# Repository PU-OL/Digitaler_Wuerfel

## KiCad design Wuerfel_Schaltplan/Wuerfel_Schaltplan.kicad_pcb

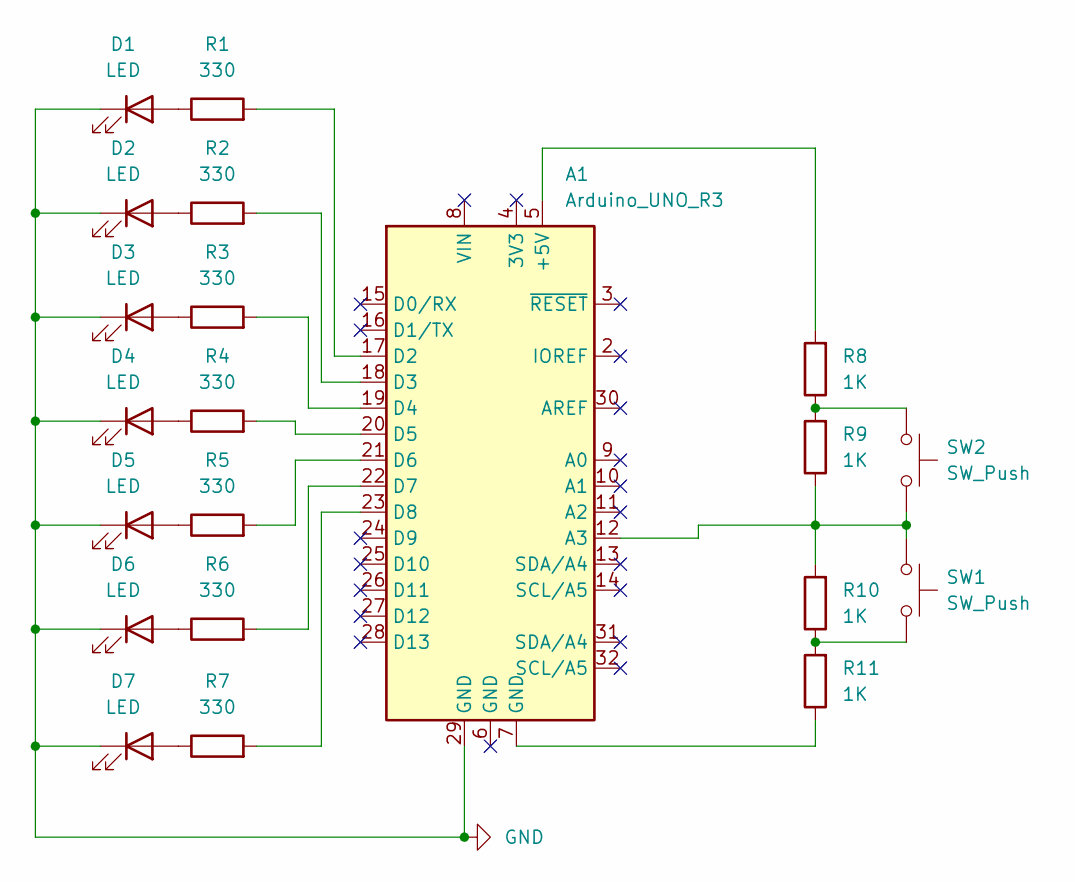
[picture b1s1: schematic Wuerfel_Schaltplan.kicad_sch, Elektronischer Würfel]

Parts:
A1: Arduino_UNO_R3; Arduino_UNO_R3_WithMountingHoles
D1, D2, D3, D4, D5, D6, D7: LED; LED_D5.0mm
R1, R2, R3, R4, R5, R6, R7: 330; R_Axial_DIN0207_L6.3mm_D2.5mm_P10.16mm_Horizontal
R8, R9, R10, R11: 1K; R_Axial_DIN0207_L6.3mm_D2.5mm_P10.16mm_Horizontal
SW1, SW2: SW_Push; SW_PUSH_6mm

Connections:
GND: A1.29 (GND), D1.1 (K), D2.1 (K), D3.1 (K), D4.1 (K), D5.1 (K), D6.1 (K), D7.1 (K)
unnamed: A1.5 (+5V), R8.2
unnamed: A1.12 (A3), R9.1, R10.2, SW1.1, SW2.2
unnamed: A1.17 (D2), R1.2
unnamed: A1.18 (D3), R2.2
unnamed: A1.19 (D4), R3.2
unnamed: A1.20 (D5), R4.2
unnamed: A1.21 (D6), R5.2
unnamed: A1.22 (D7), R6.2
unnamed: A1.23 (D8), R7.2
unnamed: A1.7 (GND), R11.1
unnamed: D1.2 (A), R1.1
unnamed: D2.2 (A), R2.1
unnamed: D3.2 (A), R3.1
unnamed: D4.2 (A), R4.1
unnamed: D5.2 (A), R5.1
unnamed: D6.2 (A), R6.1
unnamed: D7.2 (A), R7.1
unnamed: R8.1, R9.2, SW2.1
unnamed: R10.1, R11.2, SW1.2

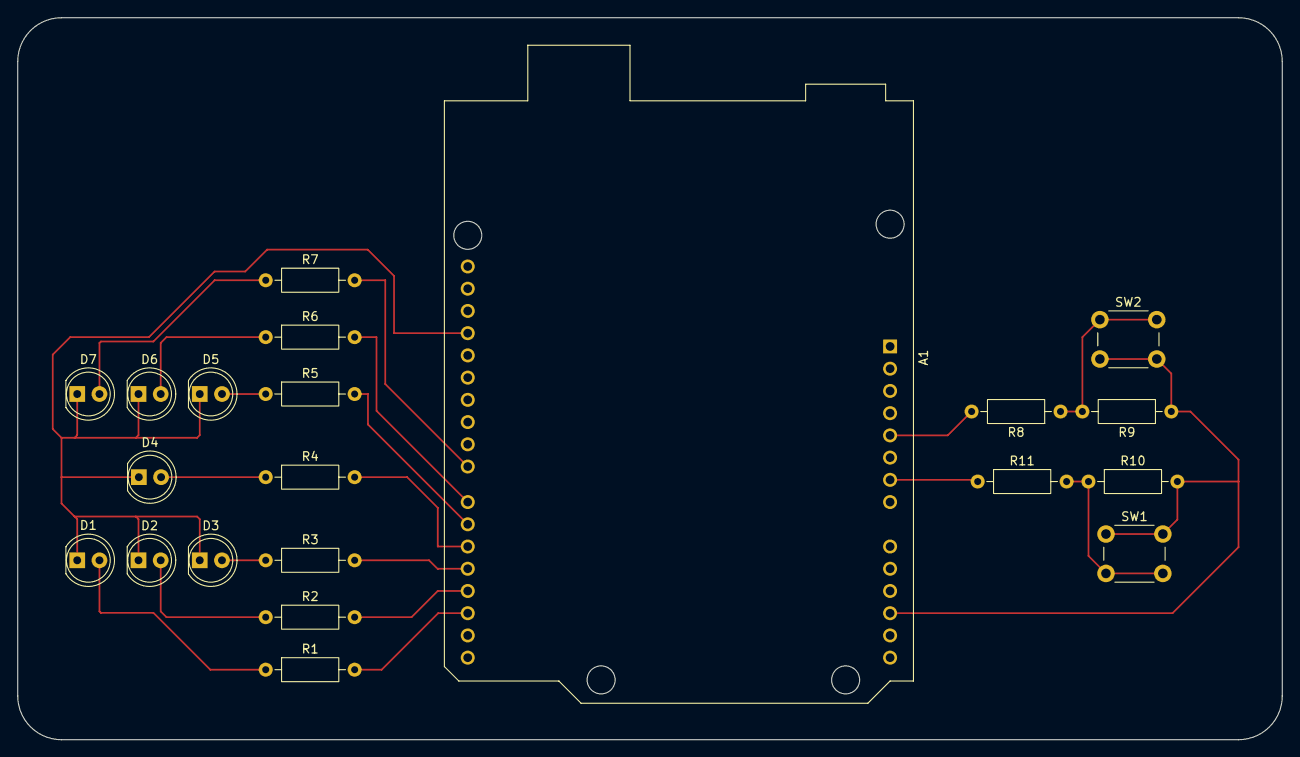
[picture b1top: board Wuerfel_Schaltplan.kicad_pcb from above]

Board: 2 copper layers, 144.5 x 82.5 mm, 21 parts (0 on the bottom side), 20 nets.
